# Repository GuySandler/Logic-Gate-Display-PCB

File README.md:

# LogicGateDisplaySolder
My first PCB showing 3 logic gates.
Made for Solder by Hackclub

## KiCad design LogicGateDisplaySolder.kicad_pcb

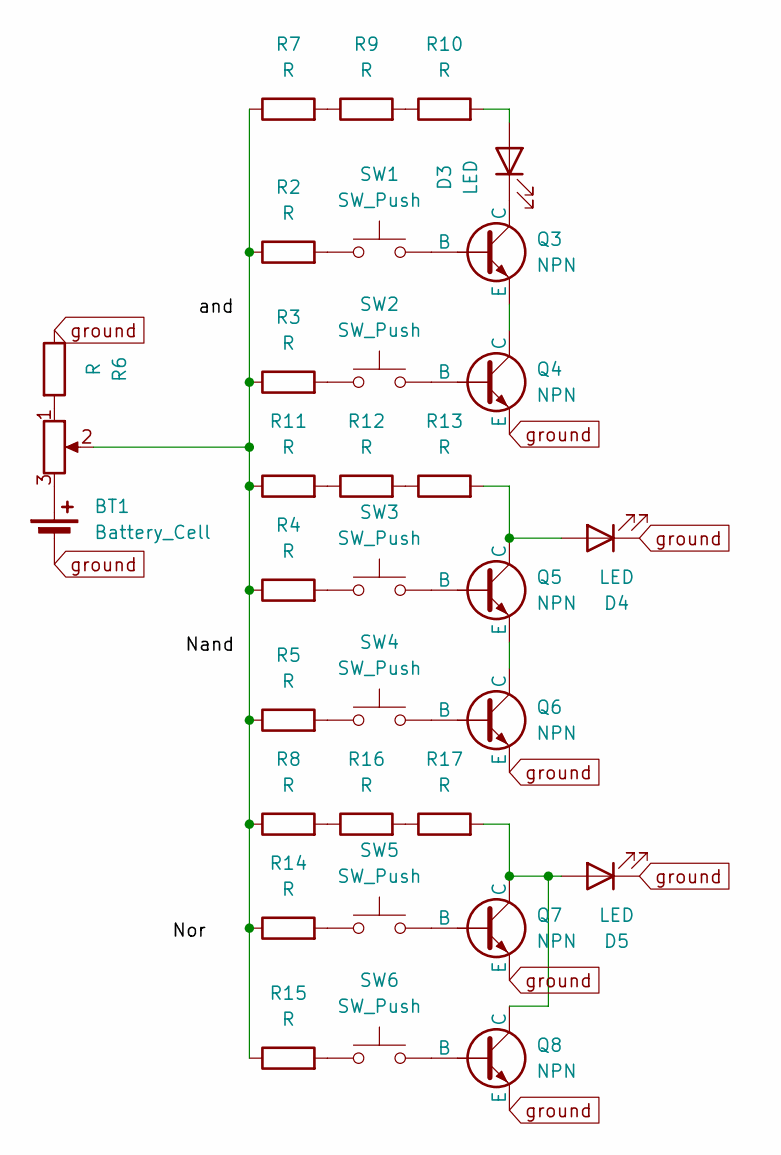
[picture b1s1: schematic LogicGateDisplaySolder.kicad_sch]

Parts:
BT1: Battery_Cell; BatteryHolder_Keystone_3034_1x20mm
D3, D4, D5: LED; LED_D5.0mm
Q3, Q4, Q5, Q6, Q7, Q8: NPN; TO-92L_HandSolder
R2, R3, R4, R5, R6, R7, R8, R9, R10, R11, R12, R13, R14, R15, R16, R17: R; R_Axial_DIN0207_L6.3mm_D2.5mm_P7.62mm_Horizontal
RV1: R_Potentiometer; Potentiometer_Vishay_T73YP_Vertical
SW1, SW2, SW3, SW4, SW5, SW6: SW_Push; SW_PUSH_6mm

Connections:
unnamed: BT1.1 (+), RV1.3
unnamed: D3.2 (A), R10.2
unnamed: D3.1 (K), Q3.1 (C)
unnamed: D4.2 (A), Q5.1 (C), R13.2
unnamed: D5.2 (A), Q7.1 (C), Q8.1 (C), R17.2
unnamed: Q3.2 (B), SW1.2
unnamed: Q3.3 (E), Q4.1 (C)
unnamed: Q4.2 (B), SW2.2
unnamed: Q5.2 (B), SW3.2
unnamed: Q5.3 (E), Q6.1 (C)
unnamed: Q6.2 (B), SW4.2
unnamed: Q7.2 (B), SW5.2
unnamed: Q8.2 (B), SW6.2
unnamed: R2.2, SW1.1
unnamed: R3.2, SW2.1
unnamed: R4.2, SW3.1
unnamed: R5.2, SW4.1
unnamed: R6.2, RV1.1
unnamed: R7.2, R9.1
unnamed: R9.2, R10.1
unnamed: R2.1, R3.1, R4.1, R5.1, R7.1, R8.1, R11.1, R14.1, R15.1, RV1.2
unnamed: R11.2, R12.1
unnamed: R12.2, R13.1
unnamed: R14.2, SW5.1
unnamed: R15.2, SW6.1
unnamed: R8.2, R16.1
unnamed: R16.2, R17.1
ground: BT1.2 (-), D4.1 (K), D5.1 (K), Q4.3 (E), Q6.3 (E), Q7.3 (E), Q8.3 (E), R6.1

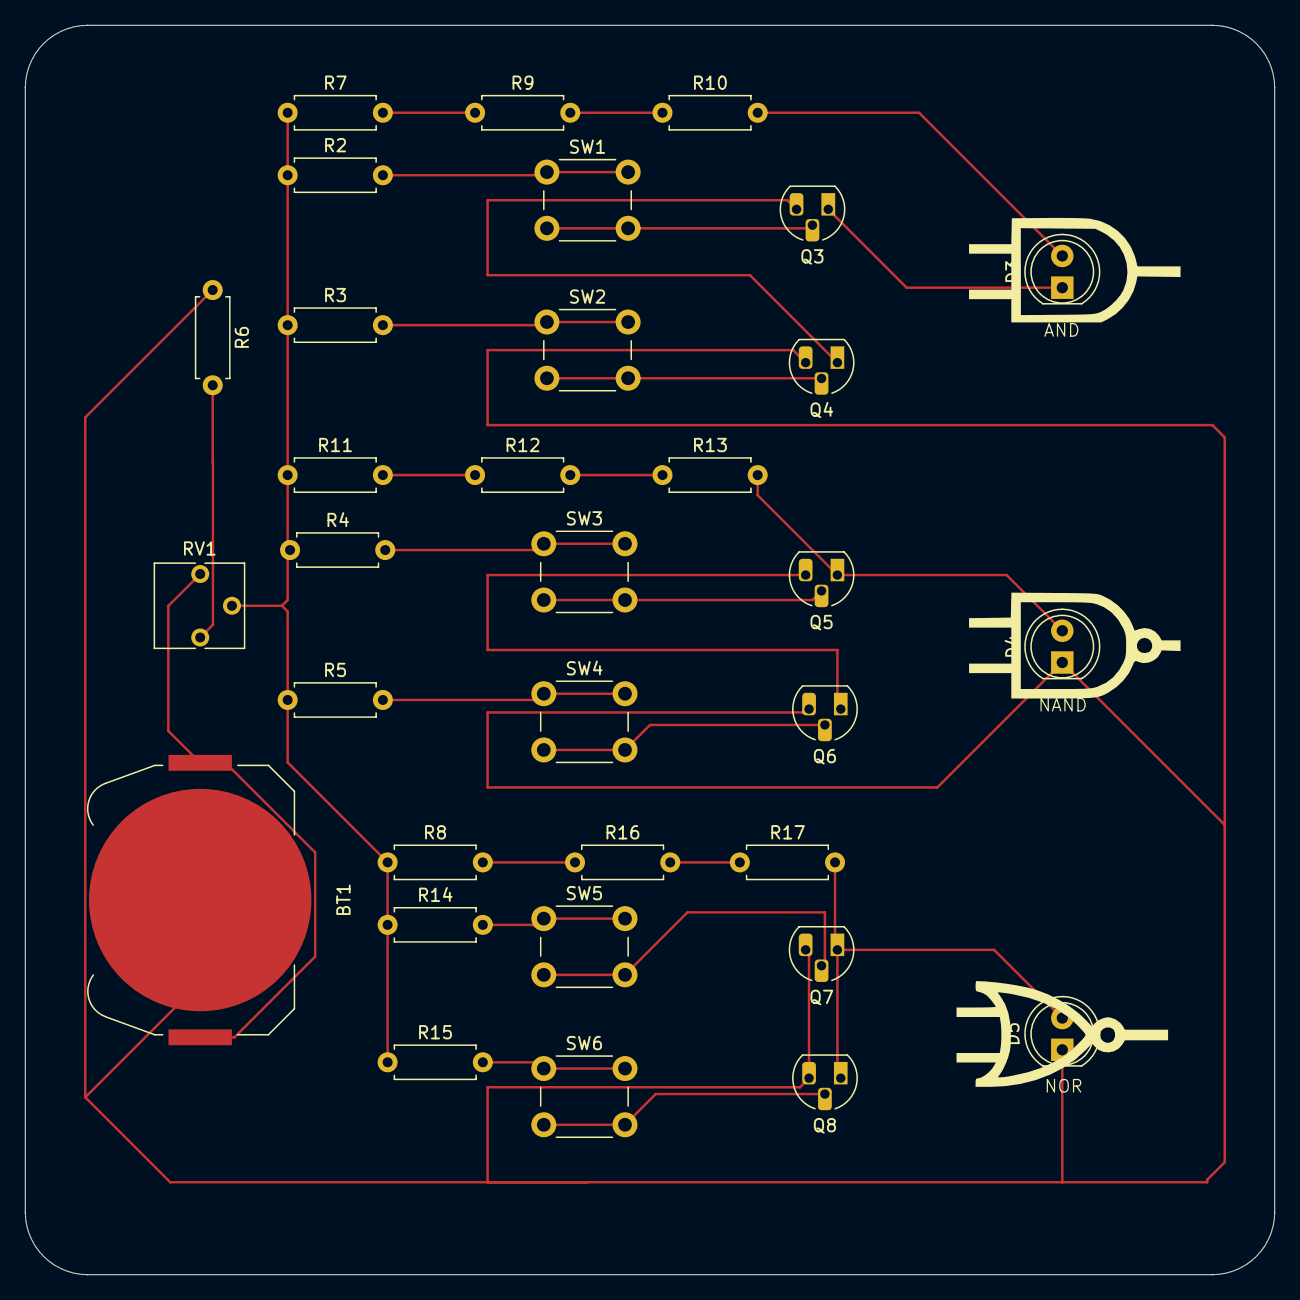
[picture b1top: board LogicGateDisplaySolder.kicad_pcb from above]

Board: 2 copper layers, 100.0 x 100.0 mm, 33 parts (0 on the bottom side), 28 nets.

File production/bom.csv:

Designator,Footprint,Quantity,Value,LCSC Part #
BT1,BatteryHolder_Keystone_3034_1x20mm,1,Battery_Cell,
C1,CP_Radial_D8.0mm_P5.00mm,1,C,
"D3, D4, D5",LED_D5.0mm,3,LED,
"Q3, Q4, Q5, Q6, Q7, Q8",TO-92L_HandSolder,6,NPN,
"R10, R11, R12, R13, R14, R15, R16, R17, R2, R3, R4, R5, R6, R7, R8, R9",R_Axial_DIN0207_L6.3mm_D2.5mm_P7.62mm_Horizontal,16,R,
RV1,Potentiometer_Vishay_T73YP_Vertical,1,R_Potentiometer,
"SW1, SW2, SW3, SW4, SW5, SW6",SW_PUSH_6mm,6,SW_Push,

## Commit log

2025-06-03 readme
